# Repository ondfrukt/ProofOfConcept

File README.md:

# Phone exchange - Proof of concept
This project aims to create an analog phone exchange for analog phones, supporting both pulse dialing and tone dialing.

This is a learning project and my personal introduction to programming, arduino and electronics. It might end up with a pile of electronic scrap and hundreds of unused disfunctional lines of code, but it will result in a lot of knowledge and a steep learning curve.

The project is coded in C++ and will use a microcontroller with wifi so that the exchange system can be govern or controlled externaly.
I'm using the [KS0835F](docs/KS0835F.pdf) modules for each phone line to monitor if the Phone hook is on or off. Them modul also generates the ring pulses to the line. A MT8816 will handle all Ain and Aout connections so that a single line is only connected to one lime at the time. The setup neads many GPIO-pins so a bucnh of MCP23017 vill be added.

A typical procedure of the system will be as shown below. A more detailed flowshart can be found [hear](docs/PhoneStatusflowshart.drawio.png)
- A hook is lifted, and the status of the line changes from "idle" to "ready."
- A phone number is dialed using pulse dialing or DTMF tones, and the digits are captured by the microcontroller.
- Ring pulses are generated for the dialed line. Once the hook is picked up, the audio lines are connected using the MT8816.
- One of the phone hooks is put down, ending the call. The audio connection is broken, and the statuses are updated accordingly.

## Phone statuses
Every phone is assigned a status for each moment, depending on how the phone is operated.

- Hook - If the phone hook is on or off due to the status
- Timer - If the new status initiate a timer
- Audio -  If a audio is played to the line due to the status (might not be implemented)
- Tone - if a tone is played to the line due to the status (might not be implemented)

| Phone status  | Function                              | Hook | Timer | Audio | Tone |
| ------------- | ------------------------------------- | ---- | ----- |-------|------| 
| idle          | Line is not in use                    | ON   | No    |
| ready         | Line is ready, waiting for inputs     | OFF  | Yes   |
| puls_dialing  | Rotary dialing in progress            | OFF  | Yes   |
| tone_dialing  | Tuch-tone dialing in progress         | OFF  | Yes   |
| busy          | Receiving busy signal                 | OFF  | Yes   |
| fail          | Line failed to connect                | OFF  | Yes   |
| ringing       | Line is ringing (outgoing call)       | OFF  | Yes   |
| connected     | Call is active                        | OFF  | No    |
| disconnected  | Call has ended, but line not yet idle | OFF  | Yes   |
| timeout       | Line timed out                        | OFF  | Yes   |
| abandoned     | Line was abandoned                    | OFF  | Yes   |
| incoming      | Incoming call                         | ON   | No    |
| operator      | Connected to operator                 | -    | No    |

## More features
- Tones are playing when a hook is picked up, during calling, and if a failure occurs. The tones must be generated by the microcontroller in some way and directed to the active lines depending on their status.
- Special audio sounds will be sent out to a certain line if you, for example, dial a secret number or try to reach 112 (911) without knowing that the phones are not connected to the main tele-network.
- Ability to receive calls from outside the network via a 4G receiver. This feature would be quite hard to implement but not impossible.
- A webpage where settings can be adjusted, line status is shown, and maybe traffic logged.
- MQTT server connection where statuses are updated.

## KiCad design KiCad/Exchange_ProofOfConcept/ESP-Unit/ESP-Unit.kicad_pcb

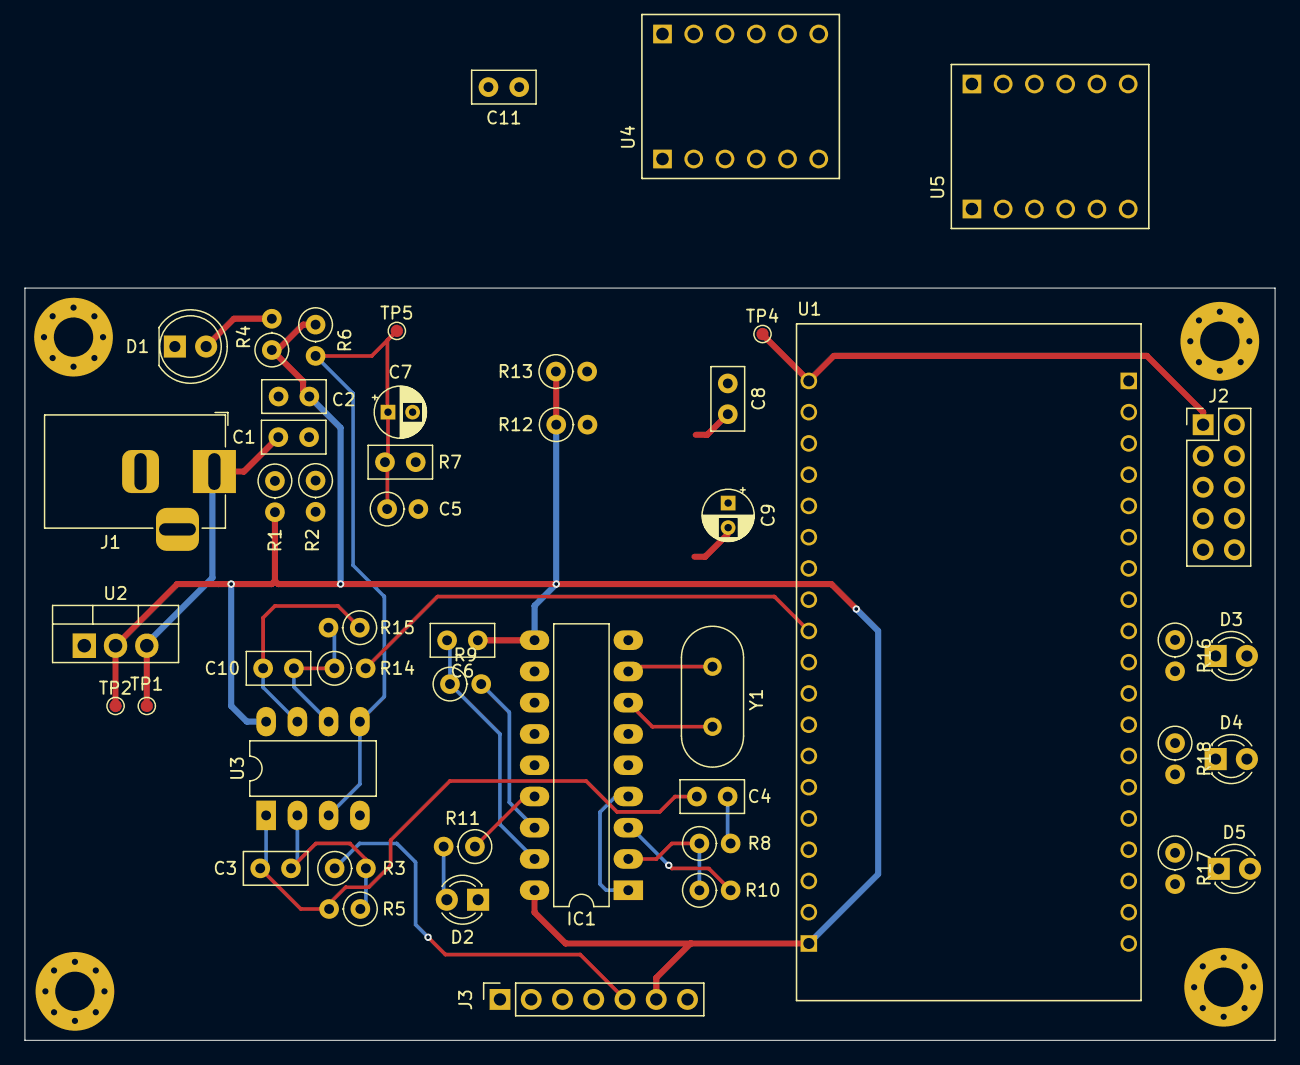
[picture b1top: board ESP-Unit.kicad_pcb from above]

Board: 2 copper layers, 101.6 x 61.1 mm, 52 parts (0 on the bottom side), 49 nets.

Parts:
C1, C4, C5, C6, C8, C11: 0,1uF; C_Disc_D5.0mm_W2.5mm_P2.50mm
C2: 10uF; C_Disc_D5.0mm_W2.5mm_P2.50mm
C3, C10: 2n2; C_Disc_D5.0mm_W2.5mm_P2.50mm
C7: 47uF; CP_Radial_D4.0mm_P2.00mm
C9: 2,2uF; CP_Radial_D4.0mm_P2.00mm
D1: LED; LED_D5.0mm
D2, D3, D4, D5: LED; LED_D3.0mm
H1, H2, H3, H4: MountingHole_Pad; MountingHole_3.2mm_M3_Pad_Via
IC1: MT8870DE; DIP-18_W7.62mm_LongPads
J1: Jack-DC; BarrelJack_Horizontal
J2: Conn_02x05_Top_Bottom; PinHeader_2x05_P2.54mm_Vertical
J3: Conn_01x07; PinSocket_1x07_P2.54mm_Vertical
R1: 240; R_Axial_DIN0207_L6.3mm_D2.5mm_P2.54mm_Vertical
R2: 720; R_Axial_DIN0207_L6.3mm_D2.5mm_P2.54mm_Vertical
R3, R5, R14, R15: 10K; R_Axial_DIN0207_L6.3mm_D2.5mm_P2.54mm_Vertical
R4, R6, R7: 470; R_Axial_DIN0207_L6.3mm_D2.5mm_P2.54mm_Vertical
R8, R10, R11: 100K; R_Axial_DIN0207_L6.3mm_D2.5mm_P2.54mm_Vertical
R9: 390K; R_Axial_DIN0207_L6.3mm_D2.5mm_P2.54mm_Vertical
R12, R13: 4,7K; R_Axial_DIN0207_L6.3mm_D2.5mm_P2.54mm_Vertical
R16, R17, R18: 220; R_Axial_DIN0207_L6.3mm_D2.5mm_P2.54mm_Vertical
TP1, TP2, TP4, TP5: TestPoint; TestPoint_Pad_D1.0mm
U1: ESP32_NODEMCU; MODULE_ESP32_NODEMCU
U2: LM317_TO-220; TO-220-3_Vertical
U3: LM358PE3; DIP-8_W7.62mm_LongPads
U4, U5: BOB-12009; CONV_BOB-12009
Y1: 3.579546; Crystal_HC49-4H_Vertical

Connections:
/3V3: C9.1, J2.1, TP4.1, U1.J5_19 (3V3), U4.LV, U5.LV
/5V: C2.1, C6.1, C8.2, C11.2, IC1.10 (TOE), IC1.18 (VDD), J3.6, R1.2, R4.1, R6.1, R12.1, R13.1, TP2.1, U1.J5_1 (5V), U2.2 (VO), U3.8 (VCC), U4.HV, U5.HV
/Audio_ESP32: R14.2, U1.J5_11 (G25)
/Audio_ESP32-Amp: C10.2, R15.1, U3.7 (2OUT)
/Audio_SLIC: J3.5, R3.1
/Audio_SLIC-Amp: C3.1, C4.2, R5.2, U3.1 (1OUT)
/Hook_Status_LED: R18.1, U1.J4_12 (G16)
/MCP_RESET: J3.4, U4.HV4
/MCP_RESET_3V: U1.J5_14 (G35), U4.LV4
/MQTT_LED: R17.2, U1.J4_11 (G17)
/Q1_3V: U1.J4_14 (G0), U5.LV4
/Q2_3V: U1.J4_15 (G2), U5.LV3
/Q3_3V: U1.J4_13 (G4), U5.LV2
/Q4_3V: U1.J4_10 (G5), U5.LV1
/SCL_3V: U1.J4_3 (G22), U4.LV2
/SDA: J3.1, R13.2, U4.HV1
/SDA_3V: U1.J4_6 (G21), U4.LV1
/SLC: J3.2, R12.2, U4.HV2
/SLIC_INT: J3.3, U4.HV3
/SLIC_INT_3V: U1.J5_15 (G34), U4.LV3
/TCK: J2.7, U1.J5_5 (G13)
/TDI: J2.9, U1.J5_7 (G12)
/TDO: J2.8, U1.J4_16 (G15)
/TMS: J2.6, U1.J5_8 (G14)
/Vref: C5.2, C7.1, R6.2, R7.1, TP5.1, U3.3 (1IN+), U3.5 (2IN+)
/WiFi_LED: R16.2, U1.J4_9 (G18)
Earth: C1.2, C2.2, C5.1, C7.2, C8.1, C11.1, D1.1 (K), D2.1 (K), D3.1 (K), D4.1 (K), D5.1 (K), H1.1, H2.1, H3.1, H4.1, IC1.5 (INH), IC1.9 (VSS), J1.2, J2.2, J2.3, J2.4, J2.5, J3.7, R2.2, R7.2, U1.J4_1 (GND_J4_1), U1.J4_7 (GND_J4_7), U1.J5_6 (GND_J5_6), U3.4 (GND), U4.GND_1 (GND), U4.GND_2 (GND), U5.GND_1 (GND), U5.GND_2 (GND)
unnamed: C4.1, R8.2
unnamed: D1.2 (A), R4.2
unnamed: D2.2 (A), R11.2
unnamed: D3.2 (A), R16.1
unnamed: D4.2 (A), R17.1
unnamed: D5.2 (A), R18.2
unnamed: IC1.16 (EST), R9.2
unnamed: IC1.3 (GS), R10.2
unnamed: IC1.1 (IN+), IC1.4 (VREF)
unnamed: IC1.2 (IN-), R8.1, R10.1
unnamed: IC1.7 (OSC1), Y1.1
unnamed: IC1.8 (OSC2), Y1.2
unnamed: IC1.11 (Q1), U5.HV4
unnamed: IC1.12 (Q2), U5.HV3
unnamed: IC1.13 (Q3), U5.HV2
unnamed: IC1.14 (Q4), U5.HV1
unnamed: IC1.15 (STD), R11.1
unnamed: C6.2, IC1.17 (ST/GT), R9.1
unnamed: R1.1, R2.1, U2.1 (ADJ)
unnamed: C1.1, J1.1, TP1.1, U2.3 (VI)
unnamed: C3.2, R3.2, R5.1, U3.2 (1IN-)
unnamed: C10.1, R14.1, R15.2, U3.6 (2IN-)

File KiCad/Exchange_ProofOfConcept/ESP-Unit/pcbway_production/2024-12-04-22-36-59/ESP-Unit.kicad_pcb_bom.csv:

Designator,Quantity,Value,Footprint,Package,MPN,DNP,Mount_Type,Description,MF,Description_1,Price,SnapEDA_Link,MP,Availability,Check_prices,MAXIMUM_PACKAGE_HEIGHT,STANDARD,MANUFACTURER
"C1, C4, C5, C6, C8, C9",6,"0,1uF",C_Disc_D5.0mm_W2.5mm_P2.50mm,,,,tht,Unpolarized capacitor,,,,,,,,,,
"C10, C3",2,2n2,C_Disc_D5.0mm_W2.5mm_P2.50mm,,,,tht,Unpolarized capacitor,,,,,,,,,,
C2,1,10uF,C_Disc_D5.0mm_W2.5mm_P2.50mm,,,,tht,Unpolarized capacitor,,,,,,,,,,
C7,1,47uF,CP_Radial_D4.0mm_P2.00mm,,,,tht,"Polarized capacitor, US symbol",,,,,,,,,,
D1,1,LED,LED_D5.0mm,,,,tht,Light emitting diode,,,,,,,,,,
"D2, D3, D4, D5",4,LED,LED_D3.0mm,,,,tht,Light emitting diode,,,,,,,,,,
"H1, H2, H3, H4",4,MountingHole_Pad,MountingHole_3.2mm_M3_Pad_Via,,,,tht,Mounting Hole with connection,,,,,,,,,,
IC1,1,MT8870DE,DIP-18_W7.62mm_LongPads,SOIC-18 Microchip,,,tht,,Microsemi Corporation,"
                        
                            Telecom IC DTMF Receiver 18-SOIC
                        
",None,https://www.snapeda.com/parts/MT8870/Microsemi+Corporation/v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,MT8870,Not in stock,https://www.snapeda.com/parts/MT8870/Microsemi+Corporation/v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,,,
J1,1,Jack-DC,BarrelJack_Horizontal,,,,tht,DC Barrel Jack,,,,,,,,,,
J2,1,Conn_02x05_Top_Bottom,PinHeader_2x05_P2.54mm_Vertical,,,,tht,"Generic connector, double row, 02x05, top/bottom pin numbering scheme (row 1: 1...pins_per_row, row2: pins_per_row+1 ... num_pins), script generated (kicad-library-utils/schlib/autogen/connector/)",,,,,,,,,,
J3,1,Conn_01x07,PinSocket_1x07_P2.54mm_Vertical,,,,tht,"Generic connector, single row, 01x07, script generated (kicad-library-utils/schlib/autogen/connector/)",,,,,,,,,,
R1,1,240,R_Axial_DIN0207_L6.3mm_D2.5mm_P2.54mm_Vertical,,,,tht,Resistor,,,,,,,,,,
"R10, R11, R8",3,100K,R_Axial_DIN0207_L6.3mm_D2.5mm_P2.54mm_Vertical,,,,tht,Resistor,,,,,,,,,,
"R12, R13",2,"4,7K",R_Axial_DIN0207_L6.3mm_D2.5mm_P2.54mm_Vertical,,,,tht,Resistor,,,,,,,,,,
"R14, R15, R3, R5",4,10K,R_Axial_DIN0207_L6.3mm_D2.5mm_P2.54mm_Vertical,,,,tht,Resistor,,,,,,,,,,
"R16, R17, R18",3,220,R_Axial_DIN0207_L6.3mm_D2.5mm_P2.54mm_Vertical,,,,tht,Resistor,,,,,,,,,,
R2,1,720,R_Axial_DIN0207_L6.3mm_D2.5mm_P2.54mm_Vertical,,,,tht,Resistor,,,,,,,,,,
"R4, R6, R7",3,470,R_Axial_DIN0207_L6.3mm_D2.5mm_P2.54mm_Vertical,,,,tht,Resistor,,,,,,,,,,
R9,1,390K,R_Axial_DIN0207_L6.3mm_D2.5mm_P2.54mm_Vertical,,,,tht,Resistor,,,,,,,,,,
"TP1, TP2, TP4, TP5",4,TestPoint,TestPoint_Pad_D1.0mm,,,,tht,test point,,,,,,,,,,
U1,1,ESP32_NODEMCU,MODULE_ESP32_NODEMCU,Package,,,tht,,AZ Delivery,"
                        
                            NodeMCU is an open source loT platform. ESP32 is a series of low cost, low power
system-on-chip (SoC) microcontrollers with integrated Wi-Fi & dual-mode Bluetooth.
                        
",None,https://www.snapeda.com/parts/ESP32%20NODEMCU/AZ-Delivery/vi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,ESP32 NODEMCU,Not in stock,https://www.snapeda.com/parts/ESP32%20NODEMCU/AZ-Delivery/vi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,6.6 mm,Manufacturer Recommendations,Espressif Systems
U2,1,LM317_TO-220,TO-220-3_Vertical,,,,tht,"1.5A 35V Adjustable Linear Regulator, TO-220",,,,,,,,,,
U3,1,LM358PE3,DIP-8_W7.62mm_LongPads,PDIP-8 Texas,,,tht,,Texas Instruments,"
                        
                            Dual, 30-V, 700-kHz operational amplifier
                        
",None,https://www.snapeda.com/parts/LM358PE3/Texas+Instruments/vie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,LM358PE3,In Stock,https://www.snapeda.com/parts/LM358PE3/Texas+Instruments/vie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,,,
"U4, U5",2,TXS0108EPWR,TSSOP-20_4.4x5mm_P0.5mm,TSSOP-20 Texas Instruments,,,smt,,Texas Instruments,"
                        
                            8-bit bidirectional voltage-level shifter for open-drain and push-pull application
                        
",None,https://www.snapeda.com/parts/TXS0108EPWR/Texas+Instruments/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,TXS0108EPWR,In Stock,https://www.snapeda.com/parts/TXS0108EPWR/Texas+Instruments/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,,,
Y1,1,3.579546,Crystal_HC49-4H_Vertical,,,,tht,Two pin crystal,,,,,,,,,,

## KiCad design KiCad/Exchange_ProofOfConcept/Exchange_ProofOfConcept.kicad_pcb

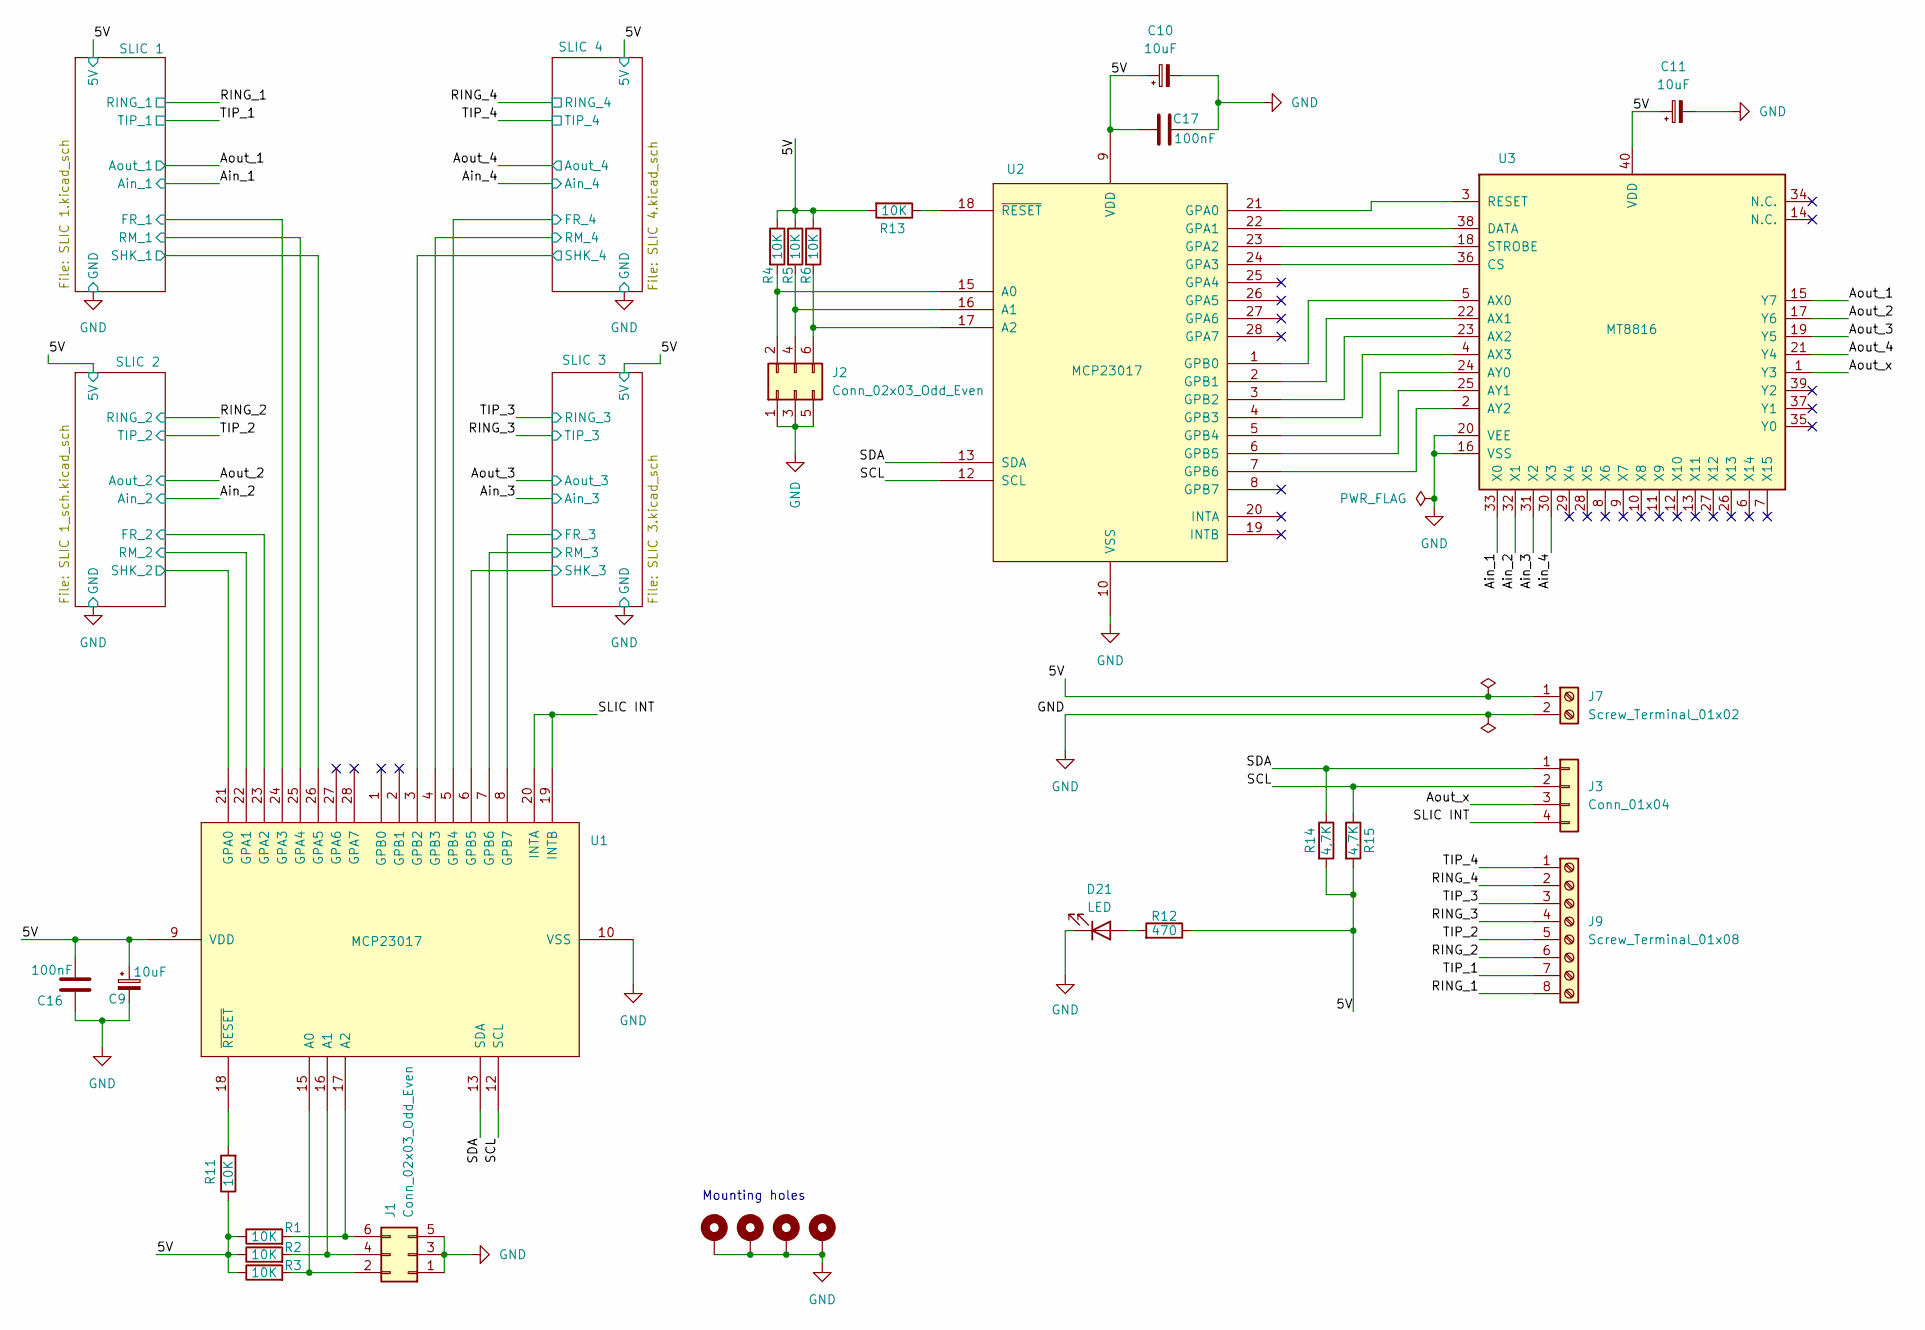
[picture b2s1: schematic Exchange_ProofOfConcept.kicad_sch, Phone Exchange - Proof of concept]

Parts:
C9, C10, C11: 10uF; CP_Radial_D4.0mm_P2.00mm
C16, C17: 100nF; C_Disc_D5.0mm_W2.5mm_P2.50mm
D21: LED; LED_D5.0mm
H1, H2, H3, H4: MountingHole_Pad; MountingHole_3.2mm_M3_Pad_Via
J1, J2: Conn_02x03_Odd_Even; PinHeader_2x03_P2.54mm_Vertical
J3: Conn_01x04; PinSocket_1x04_P2.54mm_Vertical
J7: Screw_Terminal_01x02; TerminalBlock_Phoenix_MKDS-1,5-2-5.08_1x02_P5.08mm_Horizont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
J9: Screw_Terminal_01x08; TerminalBlock_Phoenix_MKDS-1,5-8_1x08_P5.00mm_Horizontal
R1, R2, R3, R4, R5, R6, R11, R13: 10K; R_Axial_DIN0207_L6.3mm_D2.5mm_P2.54mm_Vertical
R12: 470; R_Axial_DIN0207_L6.3mm_D2.5mm_P2.54mm_Vertical
R14, R15: 4,7K; R_Axial_DIN0207_L6.3mm_D2.5mm_P2.54mm_Vertical
U1, U2: MCP23017; DIP-28_W7.62mm_Socket
U3: MT8816; DIP-40_W15.24mm_Socket_LongPads

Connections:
/Ain_1: U3.33 (X0); also elsewhere on the board
/Ain_2: U3.32 (X1); also elsewhere on the board
/Ain_3: U3.31 (X2); also elsewhere on the board
/Ain_4: U3.30 (X3); also elsewhere on the board
/Aout_1: U3.15 (Y7); also elsewhere on the board
/Aout_2: U3.17 (Y6); also elsewhere on the board
/Aout_3: U3.19 (Y5); also elsewhere on the board
/Aout_4: U3.21 (Y4); also elsewhere on the board
/RING_1: J9.8; also elsewhere on the board
/RING_2: J9.6; also elsewhere on the board
/RING_3: J9.4; also elsewhere on the board
/RING_4: J9.2; also elsewhere on the board
/SCL: J3.2, R15.1, U1.12 (SCL), U2.12 (SCL)
/SDA: J3.1, R14.1, U1.13 (SDA), U2.13 (SDA)
/SLIC 1/FR_1: U1.24 (GPA3); also elsewhere on the board
/SLIC 1/RM_1: U1.25 (GPA4); also elsewhere on the board
/SLIC 1/SHK_1: U1.26 (GPA5); also elsewhere on the board
/SLIC 2/FR_2: U1.23 (GPA2); also elsewhere on the board
/SLIC 2/RM_2: U1.22 (GPA1); also elsewhere on the board
/SLIC 2/SHK_2: U1.21 (GPA0); also elsewhere on the board
/SLIC 3/FR_3: U1.8 (GPB7); also elsewhere on the board
/SLIC 3/RM_3: U1.7 (GPB6); also elsewhere on the board
/SLIC 3/SHK_3: U1.6 (GPB5); also elsewhere on the board
/SLIC 4/FR_4: U1.5 (GPB4); also elsewhere on the board
/SLIC 4/RM_4: U1.4 (GPB3); also elsewhere on the board
/SLIC 4/SHK_4: U1.3 (GPB2); also elsewhere on the board
/TIP_1: J9.7; also elsewhere on the board
/TIP_2: J9.5; also elsewhere on the board
/TIP_3: J9.3; also elsewhere on the board
/TIP_4: J9.1; also elsewhere on the board
GND: C9.2, C10.2, C11.2, C16.1, C17.2, D21.1 (K), H1.1, H2.1, H3.1, H4.1, J1.1, J1.3, J1.5, J2.1, J2.3, J2.5, J3.7, J7.2, U1.10 (VSS), U2.10 (VSS), U3.16 (VSS), U3.20 (VEE); also elsewhere on the board
unnamed: D21.2 (A), R12.2
unnamed: J1.2, R3.2, U1.15 (A0)
unnamed: J1.4, R2.2, U1.16 (A1)
unnamed: J1.6, R1.2, U1.17 (A2)
unnamed: J2.2, R4.2, U2.15 (A0)
unnamed: J2.4, R5.2, U2.16 (A1)
unnamed: J2.6, R6.2, U2.17 (A2)
unnamed: R11.2, U1.18 (~RESET)
unnamed: U2.21 (GPA0), U3.3 (RESET)
unnamed: U2.22 (GPA1), U3.38 (DATA)
unnamed: U2.23 (GPA2), U3.18 (STROBE)
unnamed: U2.24 (GPA3), U3.36 (CS)
unnamed: U2.1 (GPB0), U3.5 (AX0)
unnamed: U2.2 (GPB1), U3.22 (AX1)
unnamed: U2.3 (GPB2), U3.23 (AX2)
unnamed: U2.4 (GPB3), U3.4 (AX3)
unnamed: U2.5 (GPB4), U3.24 (AY0)
unnamed: U2.6 (GPB5), U3.25 (AY1)
unnamed: U2.7 (GPB6), U3.2 (AY2)
unnamed: R13.1, U2.18 (~RESET)

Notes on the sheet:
Mounting holes

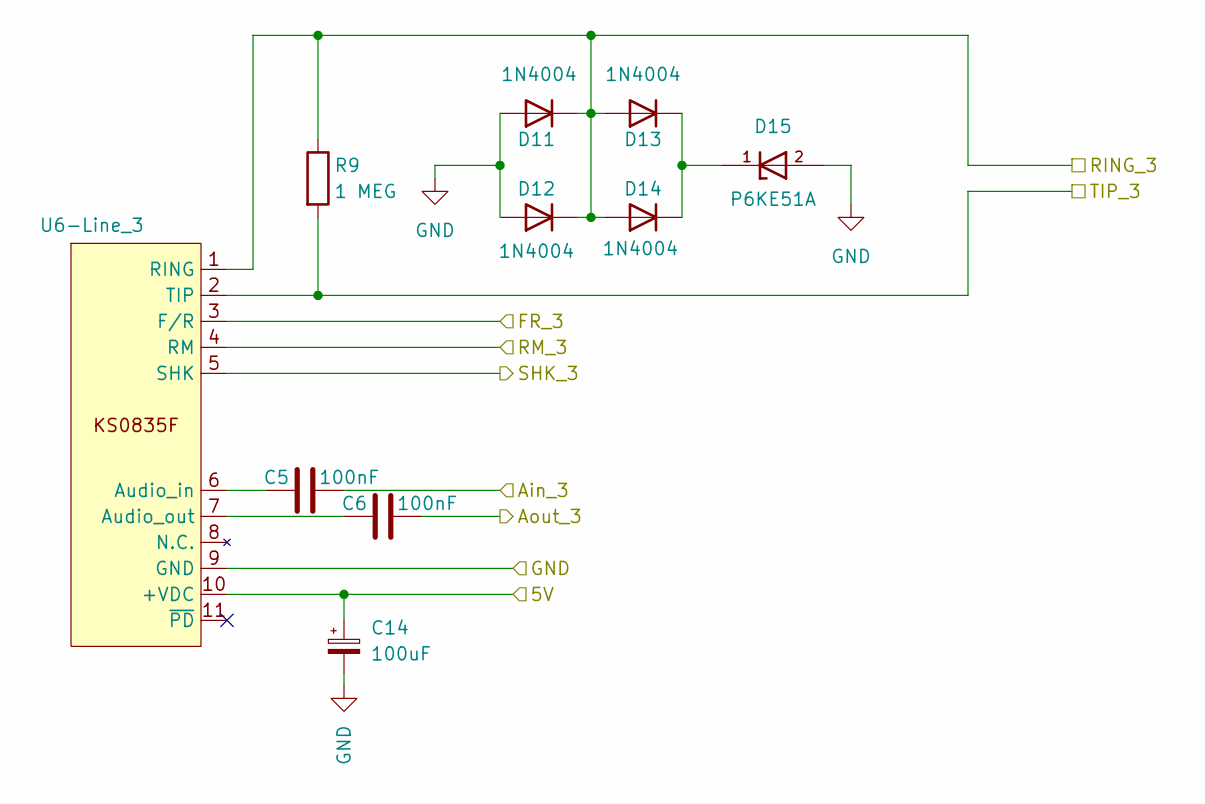
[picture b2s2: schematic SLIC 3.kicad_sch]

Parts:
C5, C6: 100nF; C_Disc_D4.3mm_W1.9mm_P5.00mm
C14: 100uF; CP_Radial_D5.0mm_P2.00mm
D11, D12, D13, D14: 1N4004; D_DO-41_SOD81_P10.16mm_Horizontal
D15: P6KE51A; D_DO-15_P12.70mm_Horizontal; PARTREV K2105
R9: 1 MEG; R_Axial_DIN0207_L6.3mm_D2.5mm_P2.54mm_Vertical
U6-Line_3: KS0835F

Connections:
/Ain_3: C5.2; also elsewhere on the board
/Aout_3: C6.2; also elsewhere on the board
/RING_3: R9.2, U6-Line_3.2 (TIP); also elsewhere on the board
/SLIC 3/FR_3: U6-Line_3.3 (F/R); also elsewhere on the board
/SLIC 3/RM_3: U6-Line_3.4 (RM); also elsewhere on the board
/SLIC 3/SHK_3: U6-Line_3.5 (SHK); also elsewhere on the board
/TIP_3: D11.1 (K), D12.1 (K), D13.2 (A), D14.2 (A), R9.1, U6-Line_3.1 (RING); also elsewhere on the board
GND: C14.2, D11.2 (A), D12.2 (A), D15.2, U6-Line_3.9 (GND); also elsewhere on the board
unnamed: D13.1 (K), D14.1 (K), D15.1
unnamed: C5.1, U6-Line_3.6 (Audio_in)
unnamed: C6.1, U6-Line_3.7 (Audio_out)

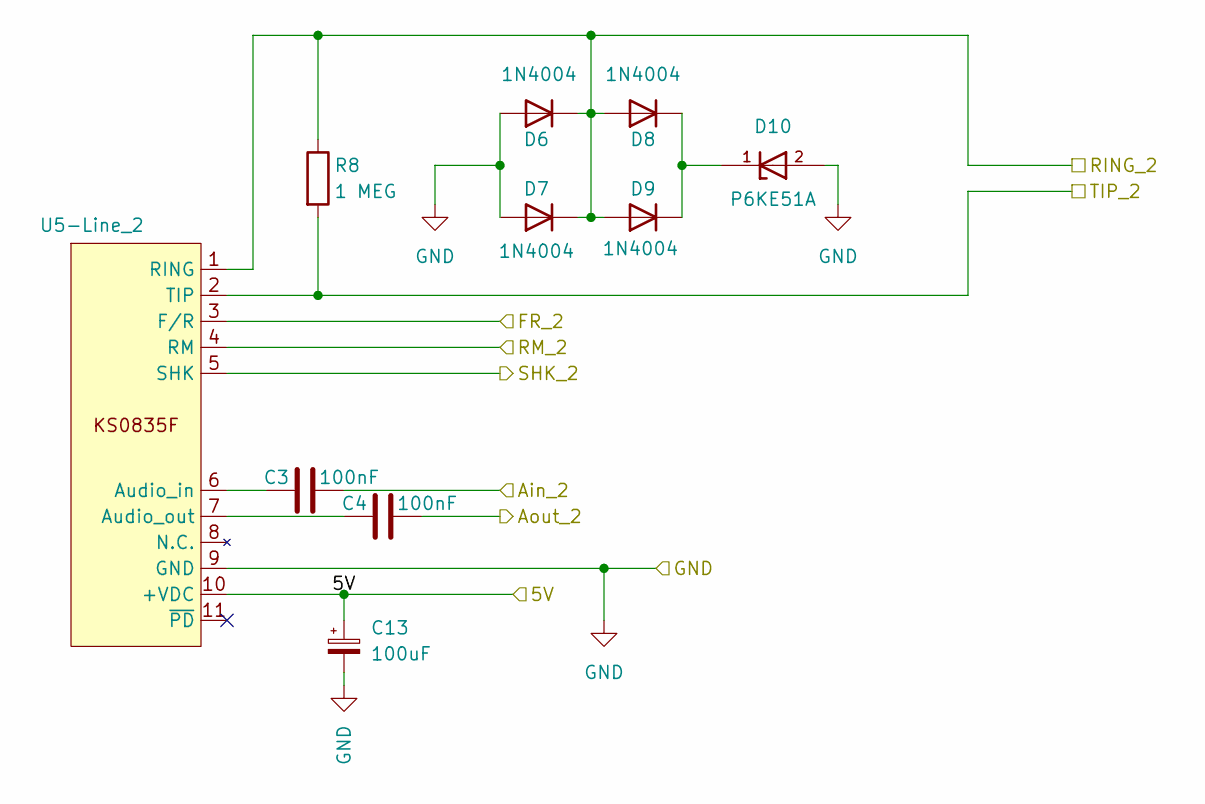
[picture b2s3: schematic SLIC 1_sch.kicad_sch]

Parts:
C3, C4: 100nF; C_Disc_D4.3mm_W1.9mm_P5.00mm
C13: 100uF; CP_Radial_D5.0mm_P2.00mm
D6, D7, D8, D9: 1N4004; D_DO-41_SOD81_P10.16mm_Horizontal
D10: P6KE51A; D_DO-15_P12.70mm_Horizontal; PARTREV K2105
R8: 1 MEG; R_Axial_DIN0207_L6.3mm_D2.5mm_P2.54mm_Vertical
U5-Line_2: KS0835F

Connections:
/Ain_2: C3.2; also elsewhere on the board
/Aout_2: C4.2; also elsewhere on the board
/RING_2: D6.1 (K), D7.1 (K), D8.2 (A), D9.2 (A), R8.1, U5-Line_2.1 (RING); also elsewhere on the board
/SLIC 2/FR_2: U5-Line_2.3 (F/R); also elsewhere on the board
/SLIC 2/RM_2: U5-Line_2.4 (RM); also elsewhere on the board
/SLIC 2/SHK_2: U5-Line_2.5 (SHK); also elsewhere on the board
/TIP_2: R8.2, U5-Line_2.2 (TIP); also elsewhere on the board
GND: C13.2, D6.2 (A), D7.2 (A), D10.2, U5-Line_2.9 (GND); also elsewhere on the board
unnamed: D8.1 (K), D9.1 (K), D10.1
unnamed: C3.1, U5-Line_2.6 (Audio_in)
unnamed: C4.1, U5-Line_2.7 (Audio_out)

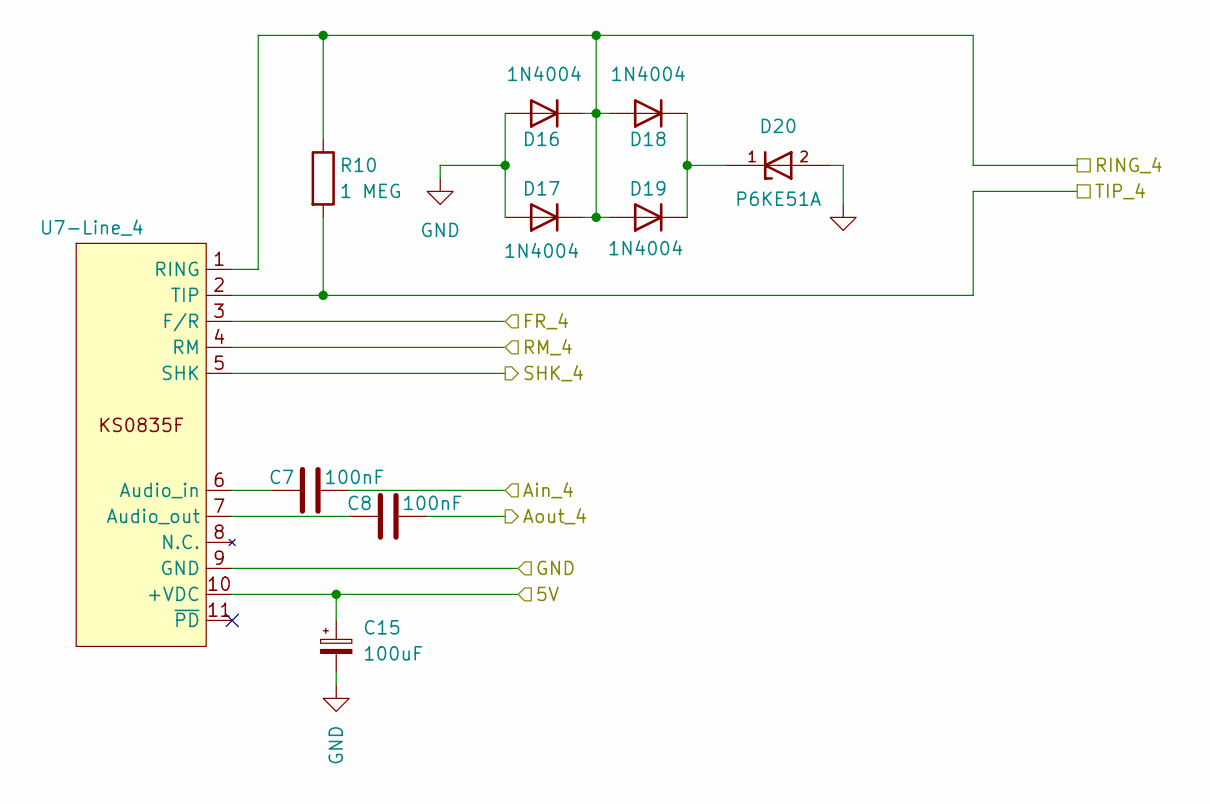
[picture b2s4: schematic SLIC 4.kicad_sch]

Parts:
C7, C8: 100nF; C_Disc_D4.3mm_W1.9mm_P5.00mm
C15: 100uF; CP_Radial_D5.0mm_P2.00mm
D16, D17, D18, D19: 1N4004; D_DO-41_SOD81_P10.16mm_Horizontal
D20: P6KE51A; D_DO-15_P12.70mm_Horizontal; PARTREV K2105
R10: 1 MEG; R_Axial_DIN0207_L6.3mm_D2.5mm_P2.54mm_Vertical
U7-Line_4: KS0835F

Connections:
/Ain_4: C7.2; also elsewhere on the board
/Aout_4: C8.2; also elsewhere on the board
/RING_4: D16.1 (K), D17.1 (K), D18.2 (A), D19.2 (A), R10.1, U7-Line_4.1 (RING); also elsewhere on the board
/SLIC 4/FR_4: U7-Line_4.3 (F/R); also elsewhere on the board
/SLIC 4/RM_4: U7-Line_4.4 (RM); also elsewhere on the board
/SLIC 4/SHK_4: U7-Line_4.5 (SHK); also elsewhere on the board
/TIP_4: R10.2, U7-Line_4.2 (TIP); also elsewhere on the board
GND: C15.2, D16.2 (A), D17.2 (A), D20.2, U7-Line_4.9 (GND); also elsewhere on the board
unnamed: D18.1 (K), D19.1 (K), D20.1
unnamed: C7.1, U7-Line_4.6 (Audio_in)
unnamed: C8.1, U7-Line_4.7 (Audio_out)

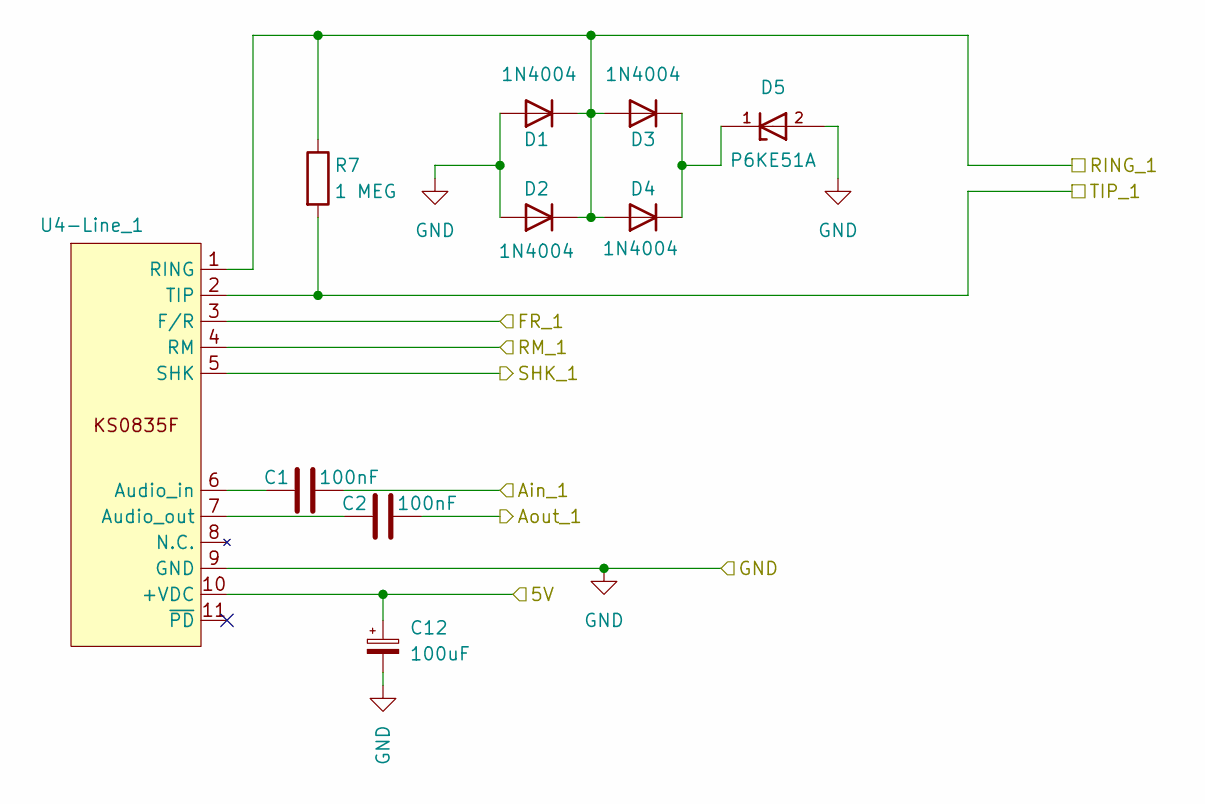
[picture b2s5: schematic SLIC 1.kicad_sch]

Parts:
C1, C2: 100nF; C_Disc_D4.3mm_W1.9mm_P5.00mm
C12: 100uF; CP_Radial_D5.0mm_P2.00mm
D1, D2, D3, D4: 1N4004; D_DO-41_SOD81_P10.16mm_Horizontal
D5: P6KE51A; D_DO-15_P12.70mm_Horizontal; PARTREV K2105
R7: 1 MEG; R_Axial_DIN0207_L6.3mm_D2.5mm_P2.54mm_Vertical
U4-Line_1: KS0835F

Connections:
/Ain_1: C1.2; also elsewhere on the board
/Aout_1: C2.2; also elsewhere on the board
/RING_1: D1.1 (K), D2.1 (K), D3.2 (A), D4.2 (A), R7.1, U4-Line_1.1 (RING); also elsewhere on the board
/SLIC 1/FR_1: U4-Line_1.3 (F/R); also elsewhere on the board
/SLIC 1/RM_1: U4-Line_1.4 (RM); also elsewhere on the board
/SLIC 1/SHK_1: U4-Line_1.5 (SHK); also elsewhere on the board
/TIP_1: R7.2, U4-Line_1.2 (TIP); also elsewhere on the board
GND: C12.2, D1.2 (A), D2.2 (A), D5.2, U4-Line_1.9 (GND); also elsewhere on the board
unnamed: D3.1 (K), D4.1 (K), D5.1
unnamed: C1.1, U4-Line_1.6 (Audio_in)
unnamed: C2.1, U4-Line_1.7 (Audio_out)

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
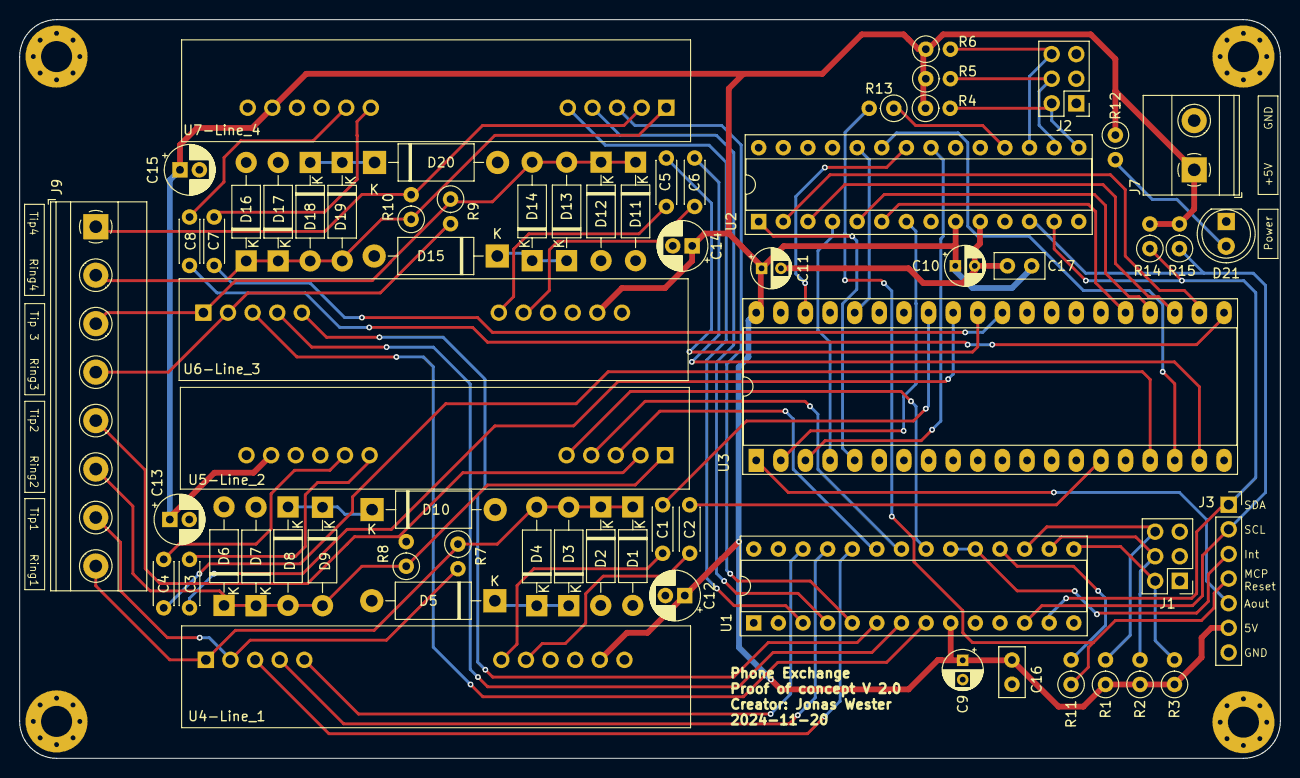
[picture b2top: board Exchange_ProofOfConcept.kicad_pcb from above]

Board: 2 copper layers, 130.0 x 76.2 mm, 69 parts (0 on the bottom side), 67 nets.

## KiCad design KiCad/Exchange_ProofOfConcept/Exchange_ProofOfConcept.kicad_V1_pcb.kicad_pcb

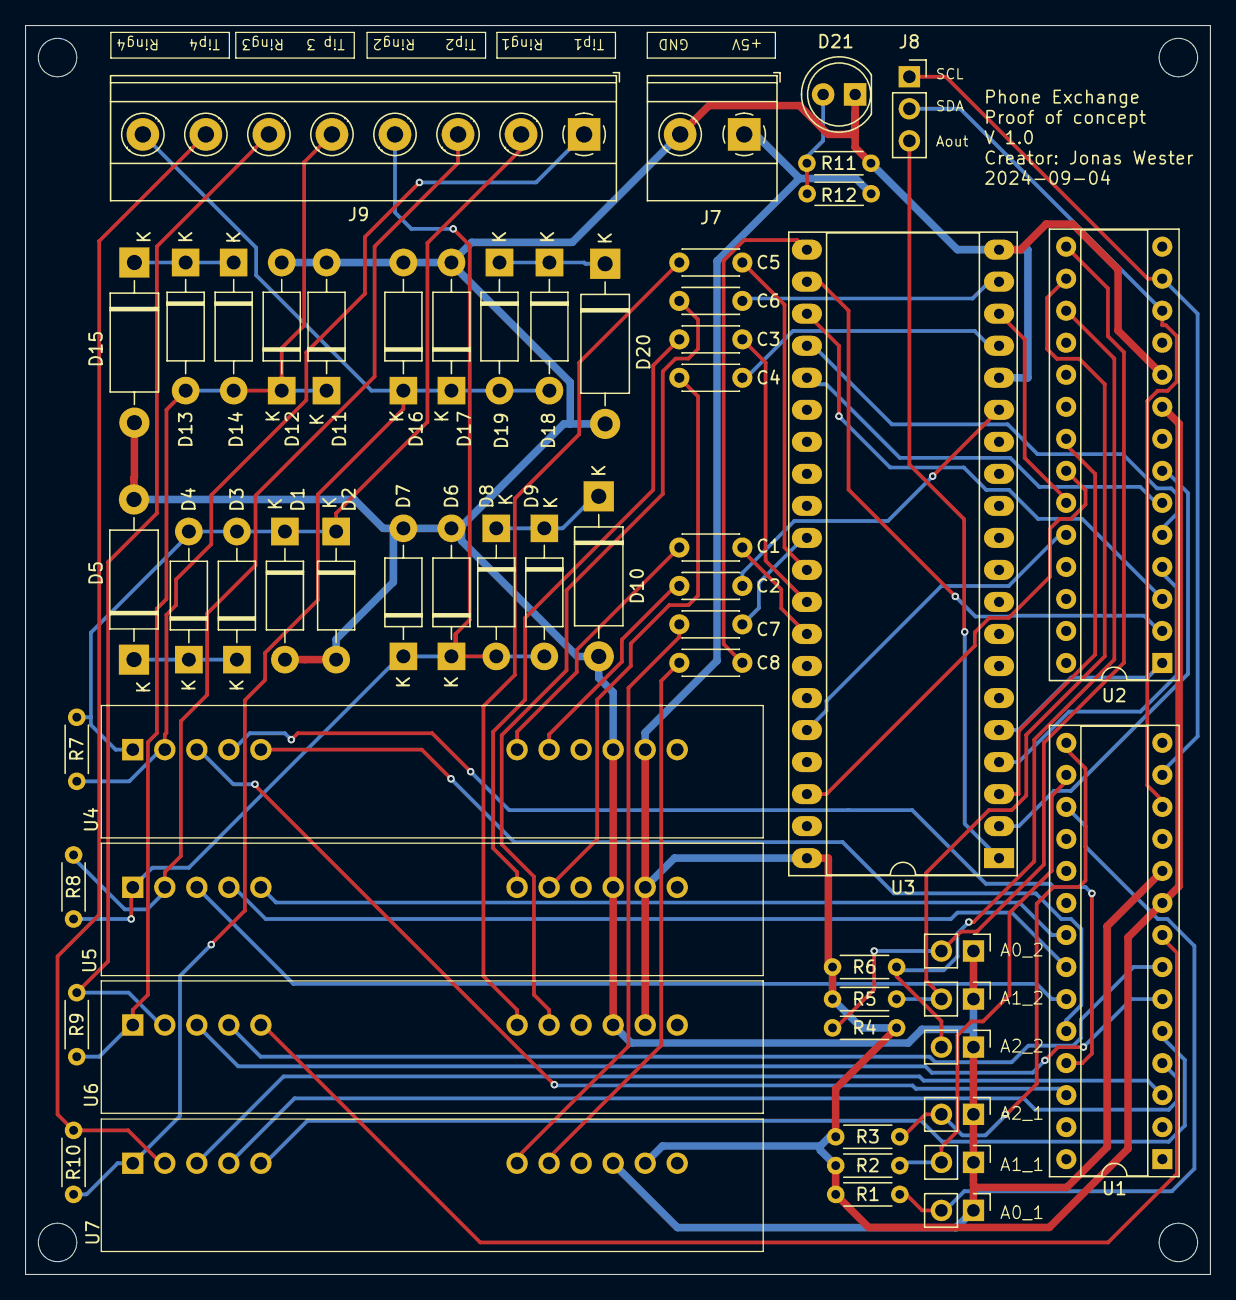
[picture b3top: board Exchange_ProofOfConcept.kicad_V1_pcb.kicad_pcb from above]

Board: 2 copper layers, 94.0 x 99.1 mm, 57 parts (0 on the bottom side), 63 nets.

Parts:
C1, C2, C3, C4, C5, C6, C7, C8: 100nF; C_Disc_D4.3mm_W1.9mm_P5.00mm
D1, D2, D3, D4, D6, D7, D8, D9, D11, D12, D13, D14, D16, D17, D18, D19: 1N4004; D_DO-41_SOD81_P10.16mm_Horizontal
D5, D10, D15, D20: P6KE51A; D_DO-15_P12.70mm_Horizontal
D21: LED; LED_D5.0mm
J1, J5, J6: Connector_PinHeader_2.54mm:PinHeader_1x02_P2.54mm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; PinHeader_1x02_P2.54mm_Vertical
J2, J3, J4: Conn_01x02; PinHeader_1x02_P2.54mm_Vertical
J7: Screw_Terminal_01x02; TerminalBlock_Phoenix_MKDS-1,5-2-5.08_1x02_P5.08mm_Horizont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
J8: Conn_01x03; PinSocket_1x03_P2.54mm_Vertical
J9: Screw_Terminal_01x08; TerminalBlock_Phoenix_MKDS-1,5-8_1x08_P5.00mm_Horizontal
R1, R2, R3, R4, R5, R6: 10K; R_Axial_DIN0204_L3.6mm_D1.6mm_P5.08mm_Horizontal
R7, R8, R9, R10: 1 MEG; R_Axial_DIN0204_L3.6mm_D1.6mm_P5.08mm_Horizontal
R11: 1K; R_Axial_DIN0204_L3.6mm_D1.6mm_P5.08mm_Horizontal
R12: 430; R_Axial_DIN0204_L3.6mm_D1.6mm_P5.08mm_Horizontal
U1, U2: MCP23017; DIP-28_W7.62mm_Socket
U3: MT8816; DIP-40_W15.24mm_Socket_LongPads
U4, U5, U6, U7: KS0835F

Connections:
/5V: J7.1, R1.1, R2.1, R3.1, R4.1, R5.1, R6.1, R12.1, U1.9 (VDD), U2.9 (VDD), U3.40 (VDD), U4.10 (+VDC), U5.10 (+VDC), U6.10 (+VDC), U7.10 (+VDC)
/Ain_1: C1.2, U3.33 (X0)
/Ain_2: C3.2, U3.32 (X1)
/Ain_3: C5.2, U3.31 (X2)
/Ain_4: C7.2, U3.30 (X3)
/Aout_1: C2.2, U3.15 (Y7)
/Aout_2: C4.2, U3.17 (Y6)
/Aout_3: C6.2, U3.19 (Y5)
/Aout_4: C8.2, U3.21 (Y4)
/Aout_x: J8.3, U3.1 (Y3)
/RING_1: D1.1 (K), D2.1 (K), D3.2 (A), D4.2 (A), J9.2, R7.1, U4.1 (RING)
/RING_2: D6.1 (K), D7.1 (K), D8.2 (A), D9.2 (A), J9.4, R8.1, U5.1 (RING)
/RING_3: J9.6, R9.2, U6.2 (TIP)
/RING_4: D16.1 (K), D17.1 (K), D18.2 (A), D19.2 (A), J9.8, R10.1, U7.1 (RING)
/SCL: J8.1, U1.13 (SDA), U2.13 (SDA)
/SDA: J8.2, U1.12 (SCL), U2.12 (SCL)
/SLIC 1/FR_1: U1.26 (GPA5), U4.3 (F/R)
/SLIC 1/RM_1: U1.25 (GPA4), U4.4 (RM)
/SLIC 1/SHK_1: U1.24 (GPA3), U4.5 (SHK)
/SLIC 2/FR_2: U1.23 (GPA2), U5.3 (F/R)
/SLIC 2/RM_2: U1.22 (GPA1), U5.4 (RM)
/SLIC 2/SHK_2: U1.21 (GPA0), U5.5 (SHK)
/SLIC 3/FR_3: U1.6 (GPB5), U6.3 (F/R)
/SLIC 3/RM_3: U1.7 (GPB6), U6.4 (RM)
/SLIC 3/SHK_3: U1.8 (GPB7), U6.5 (SHK)
/SLIC 4/FR_4: U1.3 (GPB2), U7.3 (F/R)
/SLIC 4/RM_4: U1.4 (GPB3), U7.4 (RM)
/SLIC 4/SHK_4: U1.5 (GPB4), U7.5 (SHK)
/TIP_1: J9.1, R7.2, U4.2 (TIP)
/TIP_2: J9.3, R8.2, U5.2 (TIP)
/TIP_3: D11.1 (K), D12.1 (K), D13.2 (A), D14.2 (A), J9.5, R9.1, U6.1 (RING)
/TIP_4: J9.7, R10.2, U7.2 (TIP)
GND: D1.2 (A), D2.2 (A), D5.2, D6.2 (A), D7.2 (A), D10.2, D11.2 (A), D12.2 (A), D15.2, D16.2 (A), D17.2 (A), D20.2, D21.1 (K), J1.1, J2.1, J3.1, J4.1, J5.1, J6.1, J7.2, R11.1, U1.10 (VSS), U2.10 (VSS), U3.16 (VSS), U3.20 (VEE), U4.9 (GND), U5.9 (GND), U6.9 (GND), U7.9 (GND)
unnamed: D3.1 (K), D4.1 (K), D5.1
unnamed: D8.1 (K), D9.1 (K), D10.1
unnamed: D13.1 (K), D14.1 (K), D15.1
unnamed: D18.1 (K), D19.1 (K), D20.1
unnamed: D21.2 (A), R11.2, R12.2
unnamed: J1.2, R1.2, U1.17 (A2)
unnamed: J2.2, R2.2, U1.16 (A1)
unnamed: J3.2, R3.2, U1.15 (A0)
unnamed: J4.2, R4.2, U2.15 (A0)
unnamed: J5.2, R5.2, U2.16 (A1)
unnamed: J6.2, R6.2, U2.17 (A2)
unnamed: U2.21 (GPA0), U3.3 (RESET)
unnamed: U2.22 (GPA1), U3.38 (DATA)
unnamed: U2.23 (GPA2), U3.18 (STROBE)
unnamed: U2.24 (GPA3), U3.36 (CS)
unnamed: U2.1 (GPB0), U3.5 (AX0)
unnamed: U2.2 (GPB1), U3.22 (AX1)
unnamed: U2.3 (GPB2), U3.23 (AX2)
unnamed: U2.4 (GPB3), U3.4 (AX3)
unnamed: U2.5 (GPB4), U3.24 (AY0)
unnamed: U2.6 (GPB5), U3.25 (AY1)
unnamed: U2.7 (GPB6), U3.2 (AY2)
unnamed: C1.1, U4.6 (Audio_in)
unnamed: C2.1, U4.7 (Audio_out)
unnamed: C3.1, U5.6 (Audio_in)
unnamed: C4.1, U5.7 (Audio_out)
unnamed: C5.1, U6.6 (Audio_in)
unnamed: C6.1, U6.7 (Audio_out)
unnamed: C7.1, U7.6 (Audio_in)
unnamed: C8.1, U7.7 (Audio_out)

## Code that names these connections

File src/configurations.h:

#include <Arduino.h>

// Setting up MCP for KS083F

#define GPA0 0
#define GPA1 1
#define GPA2 2
#define GPA3 3
#define GPA4 4
#define GPA5 5
#define GPA6 6
#define GPA7 7

#define GPB0 8
#define GPB1 9
#define GPB2 10
#define GPB3 11
#define GPB4 12
#define GPB5 13
#define GPB6 14
#define GPB7 15

const uint8_t SHK_1 = GPA3;
const uint8_t RM_1 = GPA4;
const uint8_t FR_1 = GPA5;

const uint8_t SHK_2 = GPA0;
const uint8_t RM_2 = GPA1;
const uint8_t FR_2 = GPA2;

const uint8_t SHK_3 = GPB4;
const uint8_t RM_3 = GPB3;
const uint8_t FR_3 = GPB2;

const uint8_t SHK_4 = GPB7;
const uint8_t RM_4 = GPB6;
const uint8_t FR_4 = GPB5;


// -----------------SHK--------------------------

// Define the number of digital inputs we want to read
#define NUM_INPUTS 4

// Array to store the pin numbers for each input
const uint8_t inputPins[NUM_INPUTS] = {SHK_1, SHK_2, SHK_3, SHK_4};

// Arrays to store debounce-related information for each input
unsigned long lastDebounceTime[NUM_INPUTS] = {0};  // Last time the input was toggled
int lastInputState[NUM_INPUTS] = {LOW};            // Previous input state
int inputState[NUM_INPUTS] = {LOW};                // Current debounced input state

// SHK Debounce time in milliseconds
uint8_t SHKDebouncing = 50;

// MCP adress
uint8_t mcp2_address = 0;
